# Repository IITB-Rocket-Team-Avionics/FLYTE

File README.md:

# FLYTE
Flight Computer for the IIT Bombay Rocket Team

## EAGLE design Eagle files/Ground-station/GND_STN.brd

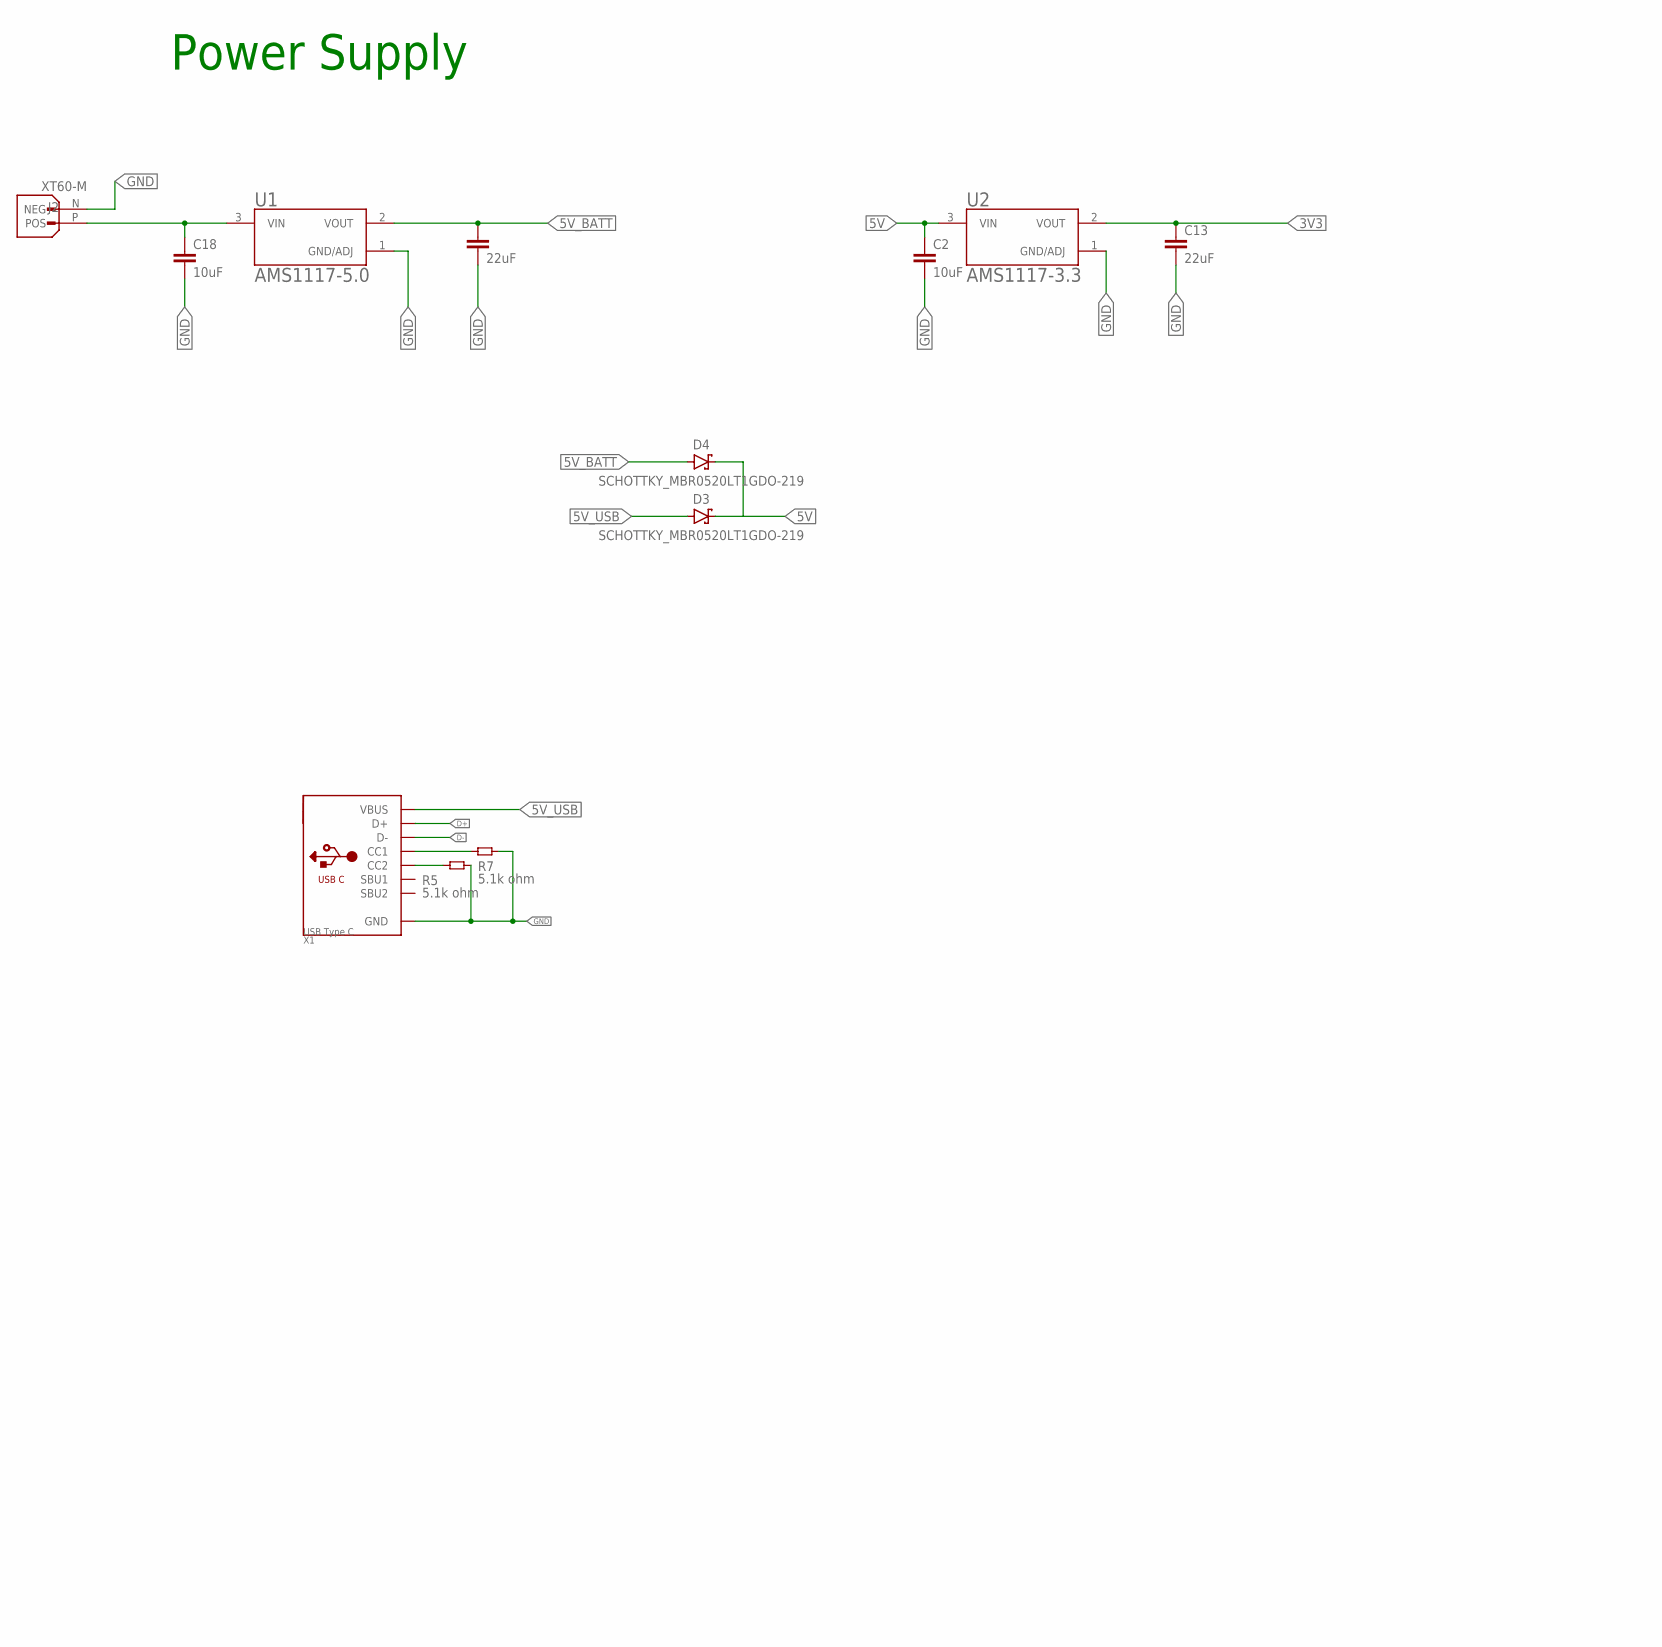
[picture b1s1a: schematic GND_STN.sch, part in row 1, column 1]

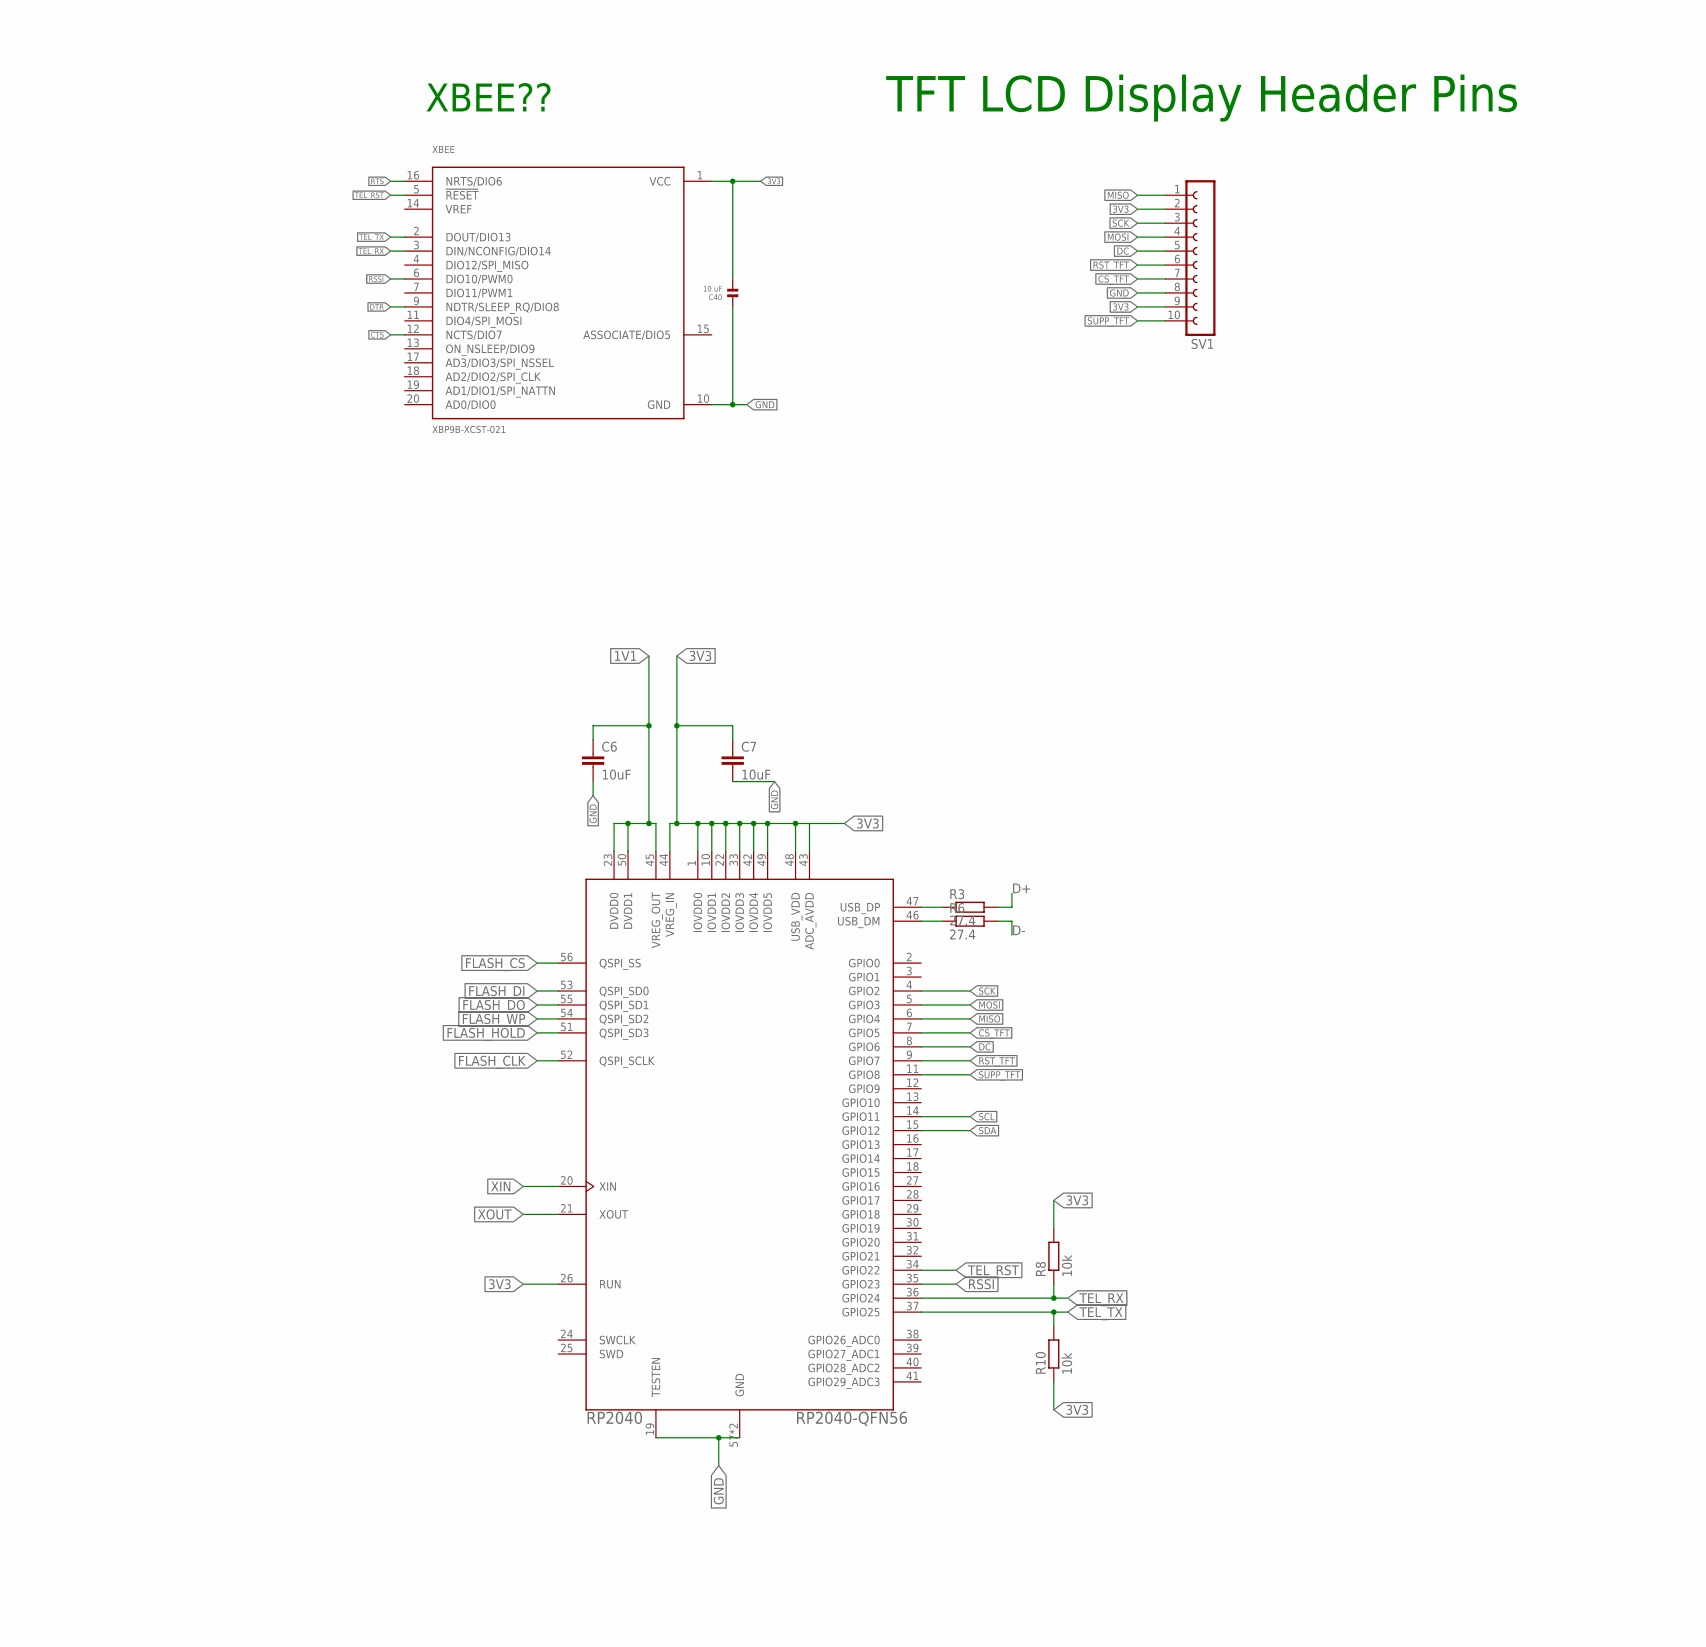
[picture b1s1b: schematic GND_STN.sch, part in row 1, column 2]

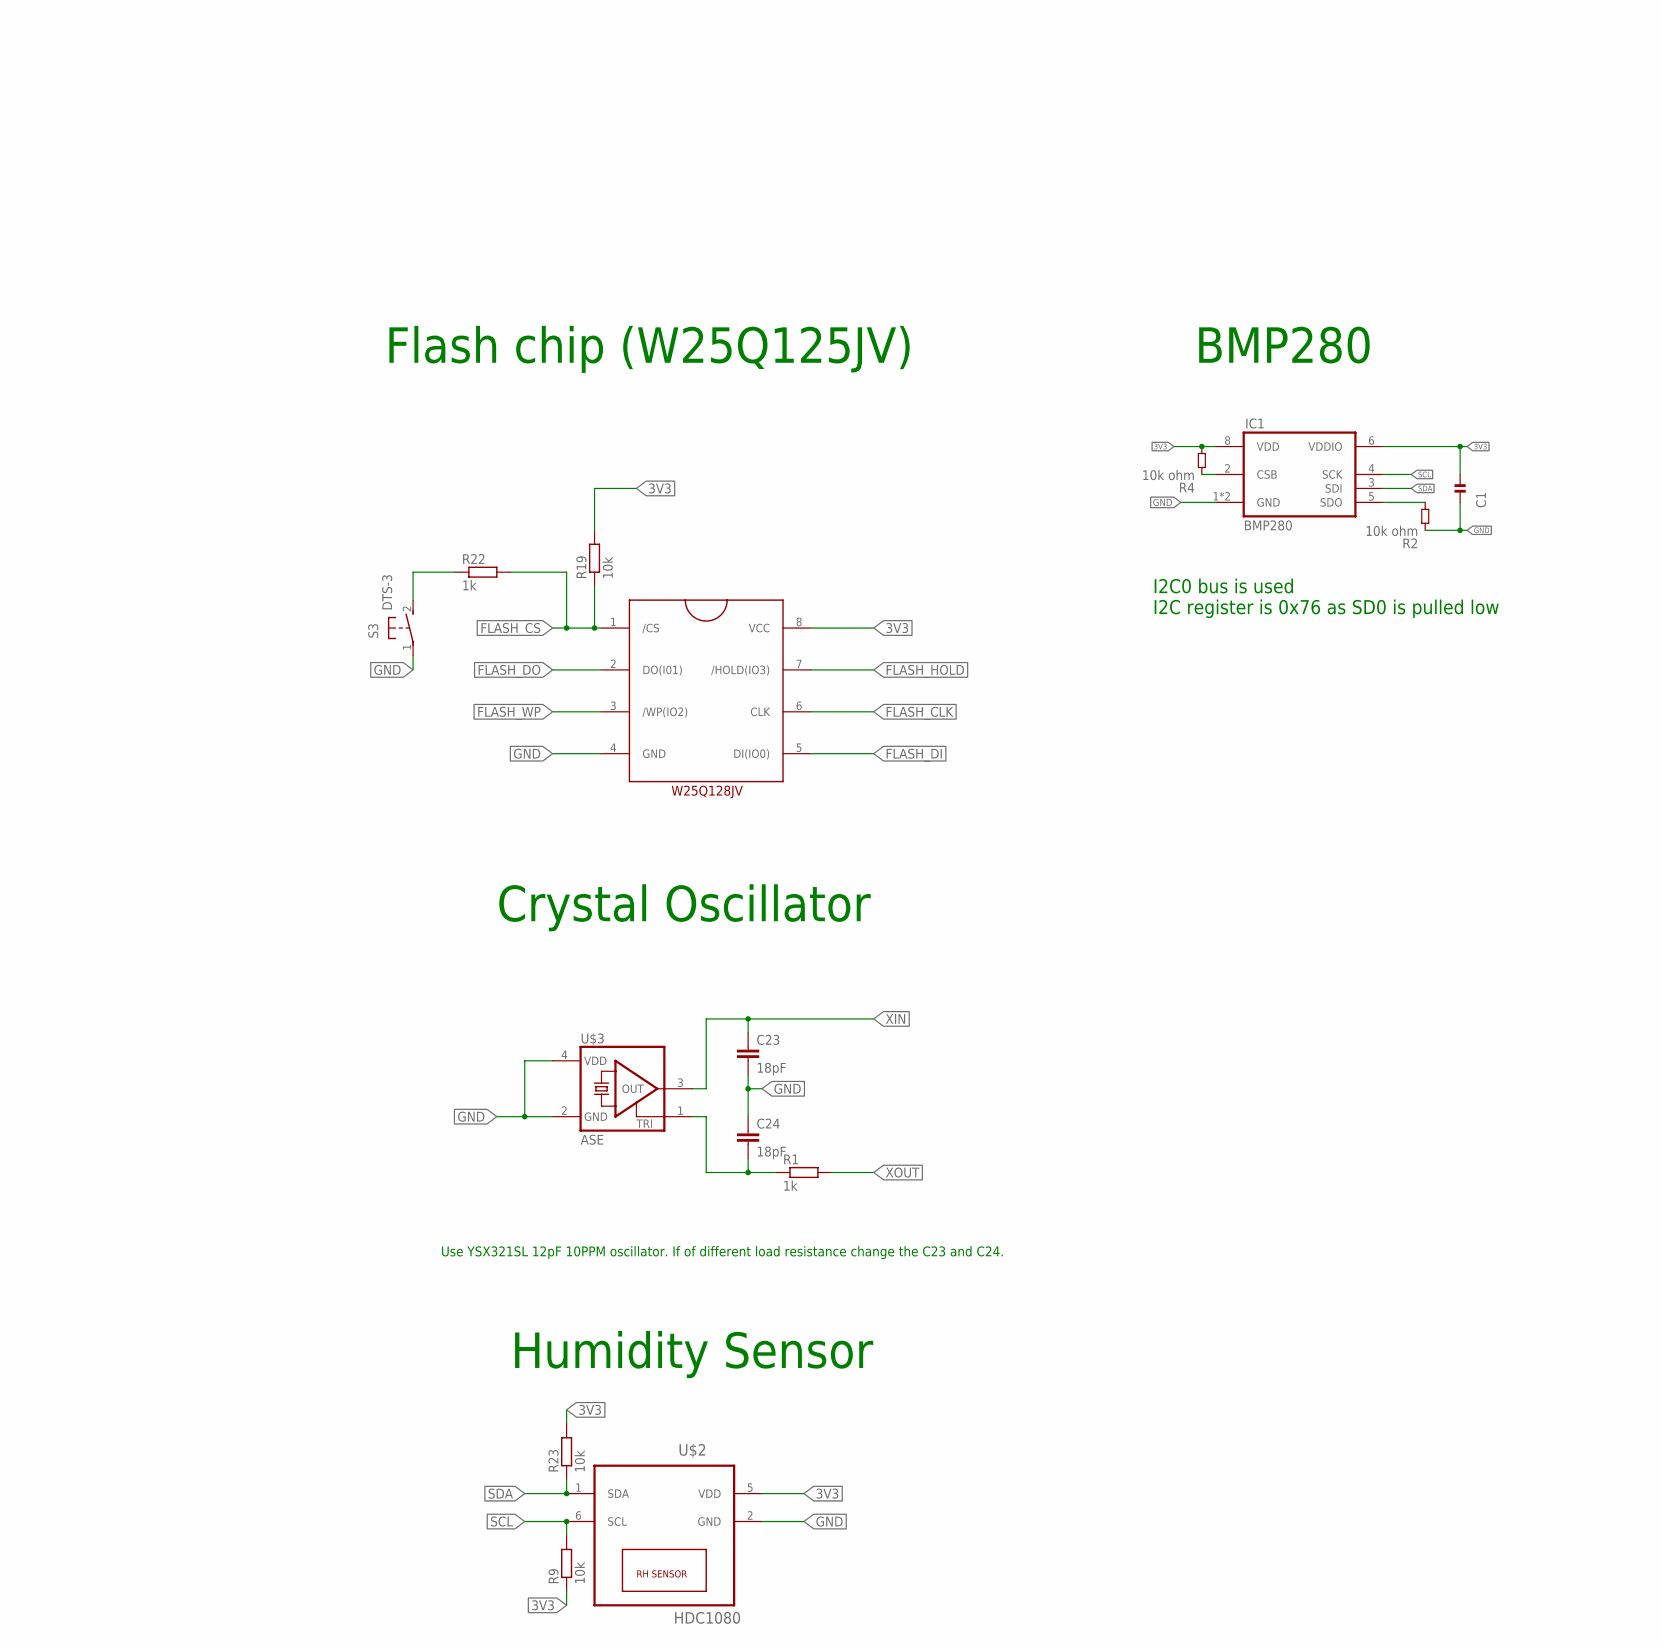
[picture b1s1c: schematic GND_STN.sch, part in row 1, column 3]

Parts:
C1, C40: 10 uF; 0603
C2, C6, C7, C18: 10uF; C0603
C3, C13: 22uF; C0603
C23, C24: 18pF; C0805
D3, D4: SCHOTTKY_MBR0520LT1GDO-219; SODFL3718X115
IC1: BMP280
J2: XT60-M; AMASS_XT60-M
R1: 1k; R0805
R2, R4: 10k ohm; 0603
R3, R6: 27.4; R0603
R5, R7: 5.1k ohm; 0603
R8, R9, R10, R19, R23: 10k; R0603
R22: 1k; R0603
RP2040: RP2040-QFN56; RP2040-QFN-56
S3: DTS-3
SV1: FE10-1; FE10
U1: AMS1117-5.0; SOT229P700X180-4N
U2: AMS1117-3.3; SOT229P700X180-4N
U4: SOIC127P790X216-8NW25Q128JVJSQ; SOIC127P790X216-8N
U$2: HDC1080; TI-S-PWSON-N6
U$3: ASE
X1: USB Type C; USB_C_CUSB31-CFM2AX-01-X
XBEE: XBP9B-XCST-021; DIP2200W51P200L3294H279Q20P

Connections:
1V1: C6.1, RP2040.23 (DVDD0), RP2040.45 (VREG_OUT), RP2040.50 (DVDD1)
3V3: C1.2, C7.1, C13.1, C40.2, IC1.6 (VDDIO), IC1.8 (VDD), R4.2, R8.2, R9.1, R10.1, R19.2, R23.2, RP2040.1 (IOVDD0), RP2040.10 (IOVDD1), RP2040.22 (IOVDD2), RP2040.26 (RUN), RP2040.33 (IOVDD3), RP2040.42 (IOVDD4), RP2040.43 (ADC_AVDD), RP2040.44 (VREG_IN), RP2040.48 (USB_VDD), RP2040.49 (IOVDD5), SV1.2, SV1.9, U2.2 (VOUT), U4.8 (VCC), U$2.5 (VDD), XBEE.1 (VCC)
5V: C2.1, D3.1 (C), D4.1 (C), U2.3 (VIN)
5V_BATT: C3.1, D4.2 (A), U1.2 (VOUT)
5V_USB: D3.2 (A), X1.A4B9 (VBUS), X1.B4A9 (VBUS)
CC3: R5.1, X1.B5 (CC2)
CC4: R7.1, X1.A5 (CC1)
CSB: IC1.2 (CSB), R4.1
CS_TFT: RP2040.7 (GPIO5), SV1.7
CTS: XBEE.12 (NCTS/DIO7)
D+: R3.2, X1.A6 (D+), X1.B6 (D+)
D-: R6.2, X1.A7 (D-), X1.B7 (D-)
DC: RP2040.8 (GPIO6), SV1.5
DTR: XBEE.9 (NDTR/SLEEP_RQ/DIO8)
FLASH_CLK: RP2040.52 (QSPI_SCLK), U4.6 (CLK)
FLASH_CS: R19.1, R22.2, RP2040.56 (QSPI_SS), U4.1 (/CS)
FLASH_DI: RP2040.53 (QSPI_SD0), U4.5 (DI(IO0))
FLASH_DO: RP2040.55 (QSPI_SD1), U4.2 (DO(I01))
FLASH_HOLD: RP2040.51 (QSPI_SD3), U4.7 (/HOLD(IO3))
FLASH_WP: RP2040.54 (QSPI_SD2), U4.3 (/WP(IO2))
GND: C1.1, C2.2, C3.2, C6.2, C7.2, C13.2, C18.2, C23.2, C24.1, C40.1, IC1.1 (GND), IC1.7 (GND), J2.N (NEG), R2.1, R5.2, R7.2, RP2040.19 (TESTEN), RP2040.57 (GND), RP2040.62 (GND), S3.1, SV1.8, U1.1 (GND/ADJ), U2.1 (GND/ADJ), U4.4 (GND), U$2.2 (GND), U$3.2 (GND), U$3.4 (VDD), X1.A1B12 (GND), X1.B1A12 (GND), XBEE.10 (GND)
MISO: RP2040.6 (GPIO4), SV1.1
MOSI: RP2040.5 (GPIO3), SV1.4
unnamed: R22.1, S3.2
unnamed: R3.1, RP2040.47 (USB_DP)
unnamed: R6.1, RP2040.46 (USB_DM)
unnamed: C24.2, R1.1, U$3.1 (TRI)
unnamed: C18.1, J2.P (POS), U1.3 (VIN)
RSSI: RP2040.35 (GPIO23), XBEE.6 (DIO10/PWM0)
RST_TFT: RP2040.9 (GPIO7), SV1.6
RTS: XBEE.16 (NRTS/DIO6)
SCK: RP2040.4 (GPIO2), SV1.3
SCL: IC1.4 (SCK), R9.2, RP2040.14 (GPIO11), U$2.6 (SCL)
SDA: IC1.3 (SDI), R23.1, RP2040.15 (GPIO12), U$2.1 (SDA)
SDO1: IC1.5 (SDO), R2.2
SUPP_TFT: RP2040.11 (GPIO8), SV1.10
TEL_RST: RP2040.34 (GPIO22), XBEE.5 (!RESET)
TEL_RX: R8.1, RP2040.36 (GPIO24), XBEE.3 (DIN/NCONFIG/DIO14)
TEL_TX: R10.2, RP2040.37 (GPIO25), XBEE.2 (DOUT/DIO13)
XIN: C23.1, RP2040.20 (XIN), U$3.3 (OUT)
XOUT: R1.2, RP2040.21 (XOUT)

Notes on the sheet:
Flash chip (W25Q125JV)
Power Supply
Crystal Oscillator
Use YSX321SL 12pF 10PPM oscillator. If of different load resistance change the C23 and C24.
I2C0 bus is used I2C register is 0x76 as SD0 is pulled low
BMP280
Humidity Sensor
TFT LCD Display Header Pins
XBEE??

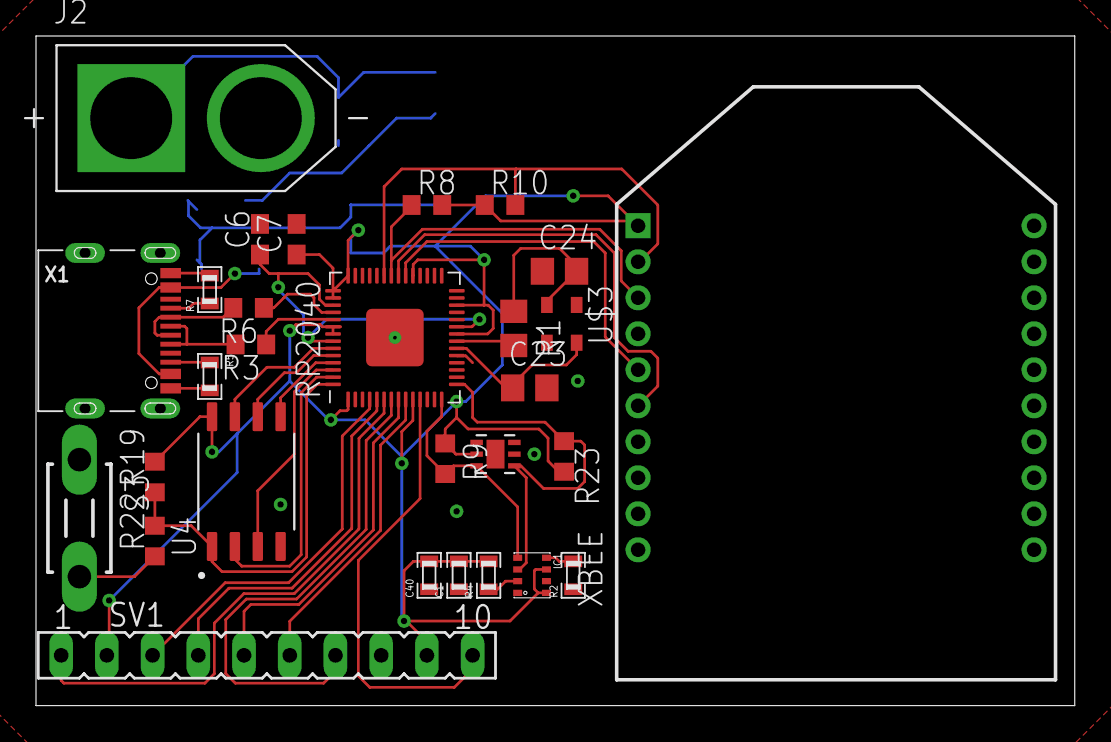
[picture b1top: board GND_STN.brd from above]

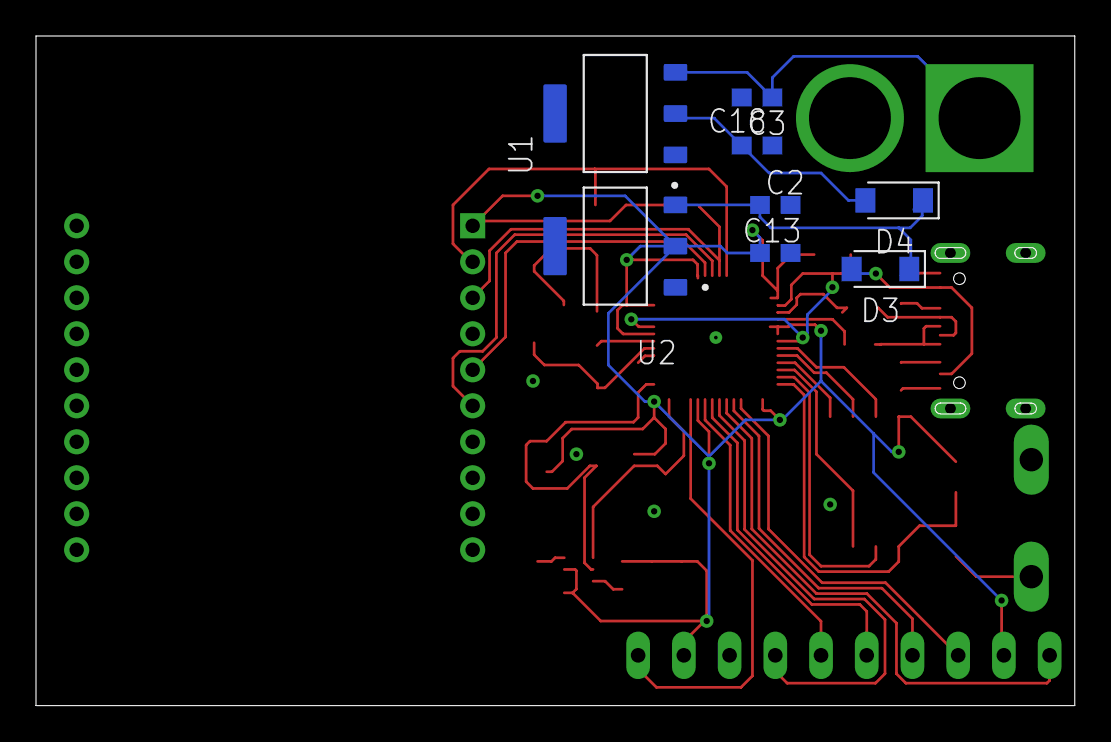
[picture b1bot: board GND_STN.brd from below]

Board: 2 copper layers, 57.7 x 37.2 mm, 37 parts (8 on the bottom side), 38 nets.

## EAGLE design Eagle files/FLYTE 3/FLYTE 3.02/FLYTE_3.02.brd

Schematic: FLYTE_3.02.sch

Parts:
AC1: KX134-1211; KX1341211
BOOT: DTSM-3
BUZZER: BUZZER; CUI_CMT-8530S-SMT
C1, C4, C5, C7, C8, C9, C10, C11, C12, C13, C14, C15, C16, C17, C19, C20, C21, C25, C26, C30, C31, C32, C34, C40, C42, C52, C62, C63: 10 uF; 0603
C2, C3: 18 pF; 0603
C6: 100 pF; 0603
C18, C27: 10\ uF; 0603
C22, C101: 100 nF; 0603
C23, C24: 27 pF; 0603
C28: 470 pF; 0603
C33, C35, C37: 120 pF; 0603
D2, D9, D10, D13: RSX501LAM20TR; SODFL4725X105N
D3, D4, D5, D6, D7, D11, D12: LED.0603; 0603.LED
FIN_1, FIN_2, FIN_3, FIN_4: 03-JST-B3B-XH-A; B3B-XH
FLASH: W25Q128JVSIQ; SOIC127P790X216-8N
GNSS: TESEO-LIV3F; SON110P970X1010X230-18N
IC1: BMP280
IC2: MPXV5100DP
IC9: MCP73844-840I_MS; SOP65P490X110-8N
J1, J3: JST-XH-2B; B2B-XH-A
J2: CON-SMA-EDGE-S; RFSOLUTIONS_CON-SMA-EDGE-S
J7: XT60-M; AMASS_XT60-M
L1: RF-INDUCTOR.0603; 0603
L2: ASPI-0630LR-220M-T15; IND_ASPI-0630LR-220M-T15
L3: 22 uH; 0603
LED: LED.0603; 0603.LED
MOTOR: 03-JST-B3B-XH-A; B3B-XH
Q1, Q3, Q4: SI7625DN-T1-GE3; SIS862DNT1GE3
Q2, Q5: MOSFET-PWIDE; SOT23-WIDE
R0, R9, R10, R11, R13, R14, R15, R17, R21, R23, R26, R30, R33, R36, R38, R46, R47, R53, R54, R55, R56, R57, R60, R61, R62, R66, R67, R68, R69, R70, R71, R72, R73, R74, R75, R76, R77, R78, R79, R80, R81, R82, R86, R87, R88, R89, R90, R91, R92, R93, R94, R95, R100, R101, R113, R114: 10k ohm; 0603
R1, R5: 1k ohm; 0603
R2, R8, R19, R29, R34, R44, R58: 100 ohm; 0603
R3, R4: 27.4 ohm; 0603
R6, R7: 5.1k ohm; 0603
R12, R22, R28, R32: 45k ohm; 0603
R16: 145k ohm; 0603
R24, R25, R27, R31, R35, R63: 0.13 ohm; 0603
R37: 30k ohm; 0603
R39, R40, R42, R43, R115, R116, R117: 0 ohm; 0603
R41: 0 ohm; 0805
R45: 190k ohm; 0603
R59: 315 ohm; 0603
R65: 100k ohm; 0603
RP2040: RP2040-QFN56; RP2040-QFN-56
SAW: SAW_FILTER; FIL_AFS14A04-1575.42-T3
U1: BNO055; LGA28R50P4X10_380X520X100
U2, U3, U5, U7, U10: CJ3400; SOT91P240X120-3N
U4: LM1117-3.3; SOT230
U6, U9, U15, U16: ADS1115IDGSR; SOP50P490X110-10N
U8, U11, U13, U14, U17: MIC29302WU-TRTO-263-5_MCH-L; TO-263-5_MCH-L
U12: CP2102; QFN50P500X500X100-29N
U19, U22: MT3608; SOT95P280X145-6N
U20: AP2210K-3.3TRG1; SOT-23-5_RAW
U$3: SN74LVC1G04DBVR; SOT23-5
X1: 22-23-2121
X6: USB Type C; USB_C_CUSB31-CFM2AX-01-X
XBEE: XBP9B-XCST-021; DIP2200W51P200L3294H279Q20P
XTAL: ASE
Y1: FC-135_32.7680KA-A0; XTAL_FC-135_32.7680KA-A0

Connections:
1V1: C8.2, RP2040.23 (DVDD0), RP2040.45 (VREG_OUT), RP2040.50 (DVDD1)
3V3: C4.2, C40.2, R39.2, R40.1, R93.2, R94.2, U4.2 (VOUT), U4.4 (VOUT_2), XBEE.1 (VCC)
3V3_OP: AC1.1 (SDO/ADDR), AC1.3 (IO_VDD), AC1.7 (VDD), AC1.10 (NCS), C10.2, C20.2, C21.1, C30.2, C32.2, FLASH.8 (VCC), GNSS.6 (VBATT), GNSS.7 (VCC_IO), GNSS.8 (VCC), IC1.6 (VDDIO), IC1.8 (VDD), R0.2, R10.2, R14.1, R39.1, R73.2, R80.2, R81.2, R82.2, R101.2, RP2040.1 (IOVDD0), RP2040.10 (IOVDD1), RP2040.22 (IOVDD2), RP2040.26 (RUN), RP2040.33 (IOVDD3), RP2040.42 (IOVDD4), RP2040.43 (ADC_AVDD), RP2040.44 (VREG_IN), RP2040.48 (USB_VDD), RP2040.49 (IOVDD5), U1.3 (VDD), U1.4 (NBOOT_LOAD_PIN), U1.28 (VDDIO), U15.7 (AIN3)
3V3_SET: C62.1, R40.2, R100.1, U12.6 (VDD)
5V: C5.2, C17.1, C26.1, IC2.2 (VS), L1.1, MOTOR.P$2, U6.8 (VDD), U9.1 (ADDR), U9.8 (VDD), U15.8 (VDD), U16.8 (VDD), U20.5 (VOUT)
BC: Q2.1 (G), R70.2, U$3.2 (A), X1.11
BUZZER: R72.2, RP2040.2 (GPIO0), U10.1 (G)
CAM: D12.P$1 (1), RP2040.4 (GPIO2), U8.1 (EN)
CC1: R7.1, X6.A5 (CC1)
CC2: R6.1, X6.B5 (CC2)
CSB: IC1.2 (CSB), R10.1
CTRL: D6.P$1 (1), RP2040.5 (GPIO3), U11.1 (EN), U13.1 (EN), U14.1 (EN), U17.1 (EN)
CTS: R115.1, XBEE.12 (NCTS/DIO7)
D1: C11.2, FIN_1.P$2, R25.2, R55.1
D2: C9.2, FIN_2.P$2, R27.2, R68.1
D3: C14.2, FIN_3.P$2, R31.2, R77.1
D4: C16.2, FIN_4.P$2, R35.2, R89.1
D+: R3.2, R41.1, X6.A6 (D+), X6.B6 (D+)
D+1: R41.2, U12.4 (D+)
D-: R4.2, U12.5 (D-), X6.A7 (D-), X6.B7 (D-)
DROGUE: R15.2, RP2040.29 (GPIO18), U5.1 (G)
DTR: R117.1, XBEE.9 (NDTR/SLEEP_RQ/DIO8)
FIN_1: FIN_1.P$1, RP2040.9 (GPIO7)
FIN_2: FIN_2.P$1, RP2040.8 (GPIO6)
FIN_3: FIN_3.P$1, RP2040.7 (GPIO5)
FIN_4: FIN_4.P$1, RP2040.6 (GPIO4)
GND: AC1.4 (TRIG), AC1.8 (GND_1), AC1.9 (GND_2), BOOT.1, C1.1, C2.1, C3.1, C4.1, C5.1, C6.1, C7.1, C8.1, C9.1, C10.1, C11.1, C12.2, C13.2, C14.1, C15.2, C16.1, C17.2, C18.1, C19.2, C20.1, C21.2, C22.1, C23.2, C24.2, C25.1, C26.2, C27.1, C28.1, C30.1, C31.1, C32.1, C34.2, C35.2, C40.1, C42.1, C52.1, C62.2, C63.2, C101.1, FIN_1.P$3, FIN_2.P$3, FIN_3.P$3, FIN_4.P$3, FLASH.4 (GND), GNSS.1 (GND), GNSS.10 (GND_RF_1), GNSS.12 (GND_RF_2), IC1.1 (GND), IC1.7 (GND), IC2.3 (GND), IC9.6 (VSS), J1.2, J2.G1 (2), J2.G2 (2), J2.G3 (2), J2.G4 (2), J3.2, J7.N (NEG), MOTOR.P$3, R2.2, R6.2, R7.2, R8.2, R9.1, R11.1, R13.1, R15.1, R17.2, R19.2, R21.1, R23.1, R26.1, R29.1, R30.1, R33.1, R34.1, R36.1, R38.1, R44.1, R46.2, R47.1, R54.2, R56.2, R58.2, R59.2, R60.2, R62.2, R67.2, R69.2, R72.1, R74.2, R76.2, R78.2, R86.2, R88.2, R90.2, R92.2, R95.1, R100.2, R101.1, R114.2, RP2040.19 (TESTEN), RP2040.57 (GND), RP2040.62 (GND), SAW.B (GND), SAW.D (GND), SAW.E (GND), U1.2 (GND), U1.5 (PS1), U1.6 (PS0), U1.10 (PIN10), U1.15 (PIN15), U1.16 (PIN16), U1.18 (COM2), U1.25 (GNDIO), U2.2 (S), U3.2 (S), U4.1 (ADJ/GND), U5.2 (S), U6.1 (ADDR), U6.3 (GND), U7.2 (S), U8.3 (GND), U8.6, U9.3 (GND), U11.3 (GND), U11.6, U12.3 (GND), U12.29 (GND), U13.3 (GND), U13.6, U14.3 (GND), U14.6, U15.3 (GND), U16.3 (GND), U17.3 (GND), U17.6, U19.2 (GND), U20.2 (GND), U22.2 (GND), U$3.3 (GND), X1.12, X6.A1B12 (GND), X6.B1A12 (GND), XBEE.10 (GND), XTAL.2 (GND), XTAL.4 (VDD)
GPS_RX: GNSS.3 (RX), R81.1, RP2040.27 (GPIO16)
GPS_TX: GNSS.2 (TX), R82.1, RP2040.28 (GPIO17)
IGN1: R36.2, RP2040.31 (GPIO20), U3.1 (G)
IGN2: R26.2, RP2040.32 (GPIO21), U2.1 (G)
LED: LED.P$1 (1), RP2040.3 (GPIO1)
MAIN: R21.2, RP2040.30 (GPIO19), U7.1 (G)
MOS: D4.P$1 (1), D13.2 (A), Q1.5 (D_1), Q1.6 (D_2), Q1.7 (D_3), Q1.8 (D_4), Q1.9 (D_5), Q1.10 (D_6), Q1.11 (D_7), X1.10
unnamed: LED.P$2 (2), R2.1
unnamed: C3.2, R5.1, XTAL.1 (TRI)
unnamed: C33.1, GNSS.11 (RF_IN)
unnamed: R12.2, R13.2, U11.5 (ADJ)
unnamed: BUZZER.N, R8.1
unnamed: D12.P$2 (2), R19.1
unnamed: IC9.1 (SENSE), Q3.1 (S_1), Q3.2 (S_2), Q3.3 (S_3), Q4.1 (S_1), Q4.2 (S_2), Q4.3 (S_3), R24.1, R63.1
unnamed: BUZZER.P, U10.2 (S)
unnamed: C22.2, U1.9 (CAP)
unnamed: R11.2, U1.17 (COM3)
unnamed: R22.2, R23.2, U13.5 (ADJ)
unnamed: R28.2, R30.2, U14.5 (ADJ)
unnamed: R32.2, R33.2, U17.5 (ADJ)
unnamed: R14.2, U1.11 (NRESET)
unnamed: D11.P$2 (2), IC9.3 (STAT1)
unnamed: C35.1, C37.2, J2.1, L1.2
unnamed: D10.2 (A), L2.2, U19.1 (SW)
unnamed: R16.2, R17.1, U19.3 (FB)
unnamed: R55.2, R56.1, U6.5 (AIN1)
unnamed: R53.2, R54.1, U6.4 (AIN0)
unnamed: C37.1, SAW.C (IN)
unnamed: D3.P$2 (2), R44.2
unnamed: C33.2, SAW.A (OUT)
unnamed: R113.2, U12.9 (!RST)
unnamed: R37.2, R38.2, U8.5 (ADJ)
unnamed: R57.2, R60.1, U6.6 (AIN2)
unnamed: R61.2, R62.1, U6.7 (AIN3)
unnamed: R66.2, R67.1, U9.4 (AIN0)
unnamed: R68.2, R69.1, U9.5 (AIN1)
unnamed: R71.2, R74.1, U9.6 (AIN2)
unnamed: R75.2, R76.1, U15.4 (AIN0)
unnamed: R77.2, R78.1, U15.5 (AIN1)
unnamed: R79.2, R86.1, U15.6 (AIN2)
unnamed: R87.2, R88.1, U16.4 (AIN0)
unnamed: R89.2, R90.1, U16.5 (AIN1)
unnamed: R91.2, R92.1, U16.6 (AIN2)
unnamed: R114.1, U12.11 (!SUSPEND)
unnamed: R115.2, U12.23 (CTS)
unnamed: R116.2, U12.24 (RTS)
unnamed: R117.2, U12.28 (DTR)
unnamed: C6.2, U20.4 (BYP)
unnamed: D9.2 (A), L3.2, U22.1 (SW)
unnamed: R45.2, R46.1, U22.3 (FB)
unnamed: C27.2, D9.1 (K), Q1.4 (G), R45.1
unnamed: D4.P$2 (2), R29.2
unnamed: D5.P$2 (2), R34.2
unnamed: D6.P$2 (2), R58.1
unnamed: D7.P$2 (2), R59.1
unnamed: IC9.4 (EN), R65.1
unnamed: IC9.8 (DRV), Q3.4 (G), Q4.4 (G)
unnamed: C101.2, IC9.5 (TIMER)
unnamed: Q5.1 (G), U$3.4 (Y)
PYRO_DROGUE: R57.1, U5.3 (D), X1.2
PYRO_IGN1: R79.1, U3.3 (D), X1.6
PYRO_IGN2: R91.1, U2.3 (D), X1.8
PYRO_MAIN: R71.1, U7.3 (D), X1.4
QSPI_SCLK: FLASH.6 (CLK), RP2040.52 (QSPI_SCLK)
QSPI_SD0: FLASH.5 (DI(IO0)), RP2040.53 (QSPI_SD0)
QSPI_SD1: FLASH.2 (DO(IO1)), RP2040.55 (QSPI_SD1)
QSPI_SD2: FLASH.3 (/WP(IO2)), RP2040.54 (QSPI_SD2)
QSPI_SD3: FLASH.7 (/HOLD/RESET(IO3)), RP2040.51 (QSPI_SD3)
QSPI_SS: FLASH.1 (/CS), R0.1, R1.2, RP2040.56 (QSPI_SS)
RSSI: RP2040.35 (GPIO23), XBEE.6 (DIO10/PWM0)
RTS: R116.1, XBEE.16 (NRTS/DIO6)
SCL: AC1.12 (SCLK/SCL), IC1.4 (SCK), R73.1, RP2040.16 (GPIO13), U1.19 (COM1), U6.10 (SCL), U9.10 (SCL), U15.1 (ADDR), U15.10 (SCL), U16.10 (SCL)
SDA: AC1.2 (SDI/SDA), IC1.3 (SDI), R80.1, RP2040.15 (GPIO12), U1.20 (COM0), U6.9 (SDA), U9.9 (SDA), U15.9 (SDA), U16.1 (ADDR), U16.9 (SDA)
SDO: IC1.5 (SDO), R9.2
TEL_RST: RP2040.34 (GPIO22), XBEE.5 (!RESET)
TEL_RX: R93.1, RP2040.36 (GPIO24), U12.26 (TXD), XBEE.3 (DIN/NCONFIG/DIO14)
TEL_TX: R94.1, RP2040.37 (GPIO25), U12.25 (RXD), XBEE.2 (DOUT/DIO13)
USB+: C25.2, L3.1, Q2.2 (S), Q5.2 (S), R47.2, R70.1, U22.4 (EN), U22.5 (IN), U$3.1 (NC), U$3.5 (VCC), X6.A4B9 (VBUS), X6.B4A9 (VBUS)
USB_BOOT: BOOT.2, R1.1
USB_BST: C18.2, D10.1 (K), D11.P$1 (1), IC9.2 (VDD), R16.1, R24.2, R63.2, R65.2
USB_CHG: C52.2, L2.1, Q2.3 (D), R95.2, U19.4 (EN), U19.5 (IN)
USB_DM: R4.1, RP2040.46 (USB_DM)
USB_DP: R3.1, RP2040.47 (USB_DP)
VBUS: Q5.3 (D), R42.1, R43.2
VBUS_OP: D2.2 (A), D5.P$1 (1), R42.2
VBUS_SET: C63.1, D3.P$1 (1), R43.1, R113.1, U12.7 (REGIN), U12.8 (VBUS)
VCC: C1.2, C7.2, C34.1, D2.1 (K), D13.1 (K), U4.3 (VIN), U8.2 (IN), U10.3 (D), U20.1 (VIN), U20.3 (EN)
VCC_PYRO: D7.P$1 (1), X1.1, X1.3, X1.5, X1.7, X1.9
VOLT_DP: C28.2, IC2.4 (VOUT), U16.7 (AIN3)
VOLT_MOTOR: MOTOR.P$1, U9.7 (AIN3)
V_CAM: C31.2, J1.1, J3.1, R37.1, U8.4 (OUT)
V_FIN_1: R12.1, R25.1, R53.1, U11.4 (OUT)
V_FIN_2: R22.1, R27.1, R66.1, U13.4 (OUT)
V_FIN_3: R28.1, R31.1, R75.1, U14.4 (OUT)
V_FIN_4: R32.1, R35.1, R87.1, U17.4 (OUT)
XIN: C2.2, RP2040.20 (XIN), XTAL.3 (OUT)
XIN32: C23.1, U1.27 (XIN32), Y1.1
XOUT: R5.2, RP2040.21 (XOUT)
XOUT32: C24.1, U1.26 (XOUT32), Y1.2
XT60+: C12.1, C13.1, C15.1, C19.1, C42.2, IC9.7 (VBAT), J7.P (POS), Q1.1 (S_1), Q1.2 (S_2), Q1.3 (S_3), Q3.5 (D_1), Q3.6 (D_2), Q3.7 (D_3), Q3.8 (D_4), Q3.9 (D_5), Q3.10 (D_6), Q3.11 (D_7), Q4.5 (D_1), Q4.6 (D_2), Q4.7 (D_3), Q4.8 (D_4), Q4.9 (D_5), Q4.10 (D_6), Q4.11 (D_7), R61.1, U11.2 (IN), U13.2 (IN), U14.2 (IN), U17.2 (IN)

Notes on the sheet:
FLASH
USB
RP2040
CRYSTAL OSCILLATOR
VBUS : Power from USB D+ : Data line 1 D- : Data line 2 CC1 & CC2 : Not sure what they are for but both must be pulled to GND using 5.1k ohm resistors when using Type-C USB SHLD : Outer covering of female USB connector. Should be grounded GND : Ground Try to route D+ and D- so that the differential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
Power C9-C16 : Decoupling capacitors for RP2040. Must be placed close to the power pins. C8 must be close to Pin 45, C10 must be close to Pin 44, rest can be jumbled around as you may like. There is one decoupling capacitor less than number of power pins. Not sure why, that's just how it is in the 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
Power C5 - Decoupling capacitor for flash. Must pe placed close to the flash. Boot When CS is pulled LOW on startup by pressing the button, the flash boots up as a mass storage device (like an SD Card). This is similar to plugging in a USB cable into a Pico while holding the BOOTSEL button. As a pr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
Purchase Links LED : https://evelta.com/green-led-smd-0603-package/ Buzzer : https://www.sunrom.com/p/electromagnetic-passive-buzzer-3-5v-smd-pcb-mount-mlt-8530
Crystal oscillators need a load capacitance to osciallte at the right frequency. This particular chip needs 12 pF. So, 2 capacitors of 22 pF each are placed to give an equivalent load capacitance of 11 pF. 24 pF capacitors were not available, but these get the job done. 1k ohm resistor to ensure th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
TESEO-LIV3F : GNSS Chip TX & RX : For UART communication SCL & SDA : For I2C communication PPS : Time pulse from GNSS VCC_RF : Power output from chip to active antenna C20 & C22 : Blocks DC voltage C18 & C21 : Decoupling capacitors GNSS_SWITCH : Used to switch between 3 antennae V1 : 0, V2 : 0 - RF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
GNSS
Telemetry communicates with pico on SPI0 bus

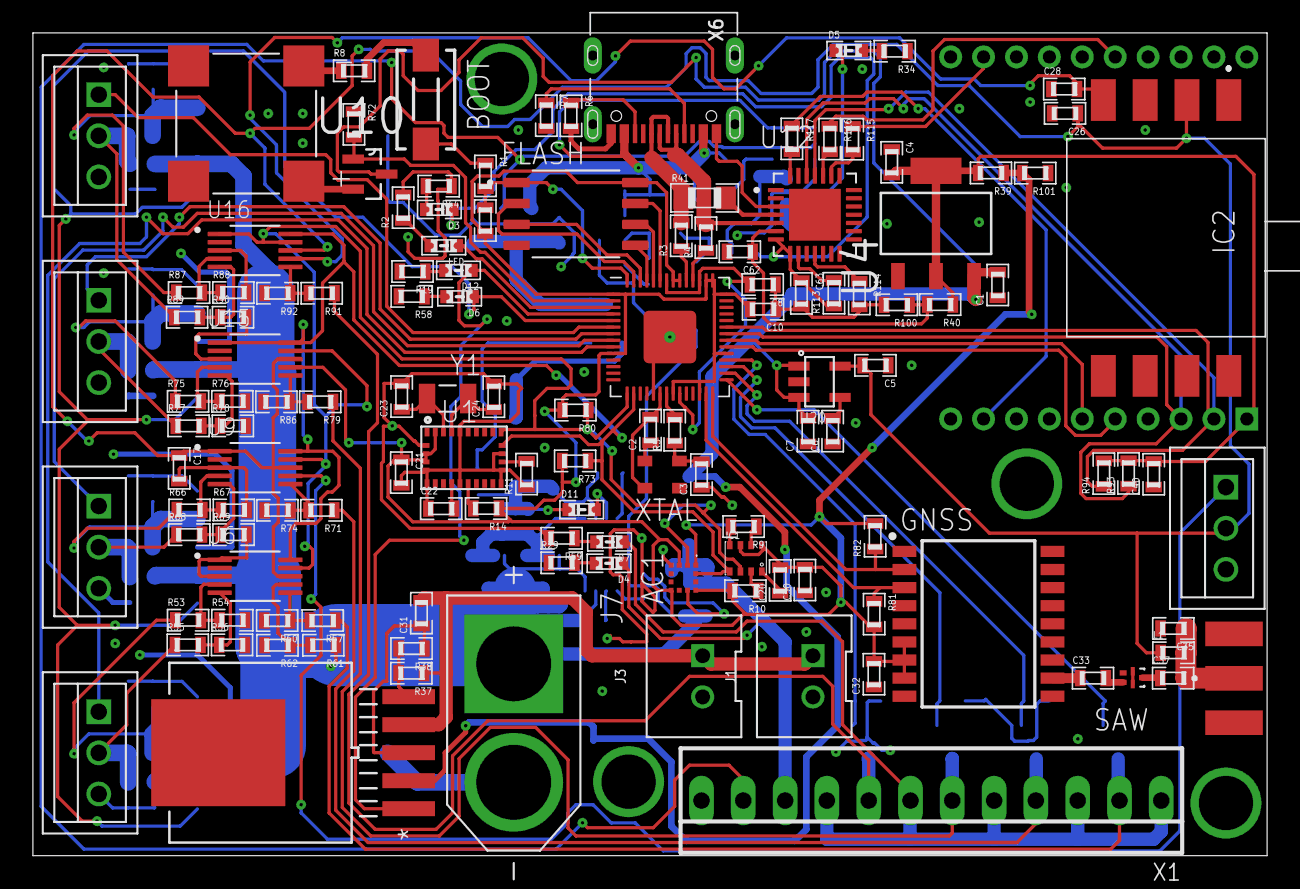
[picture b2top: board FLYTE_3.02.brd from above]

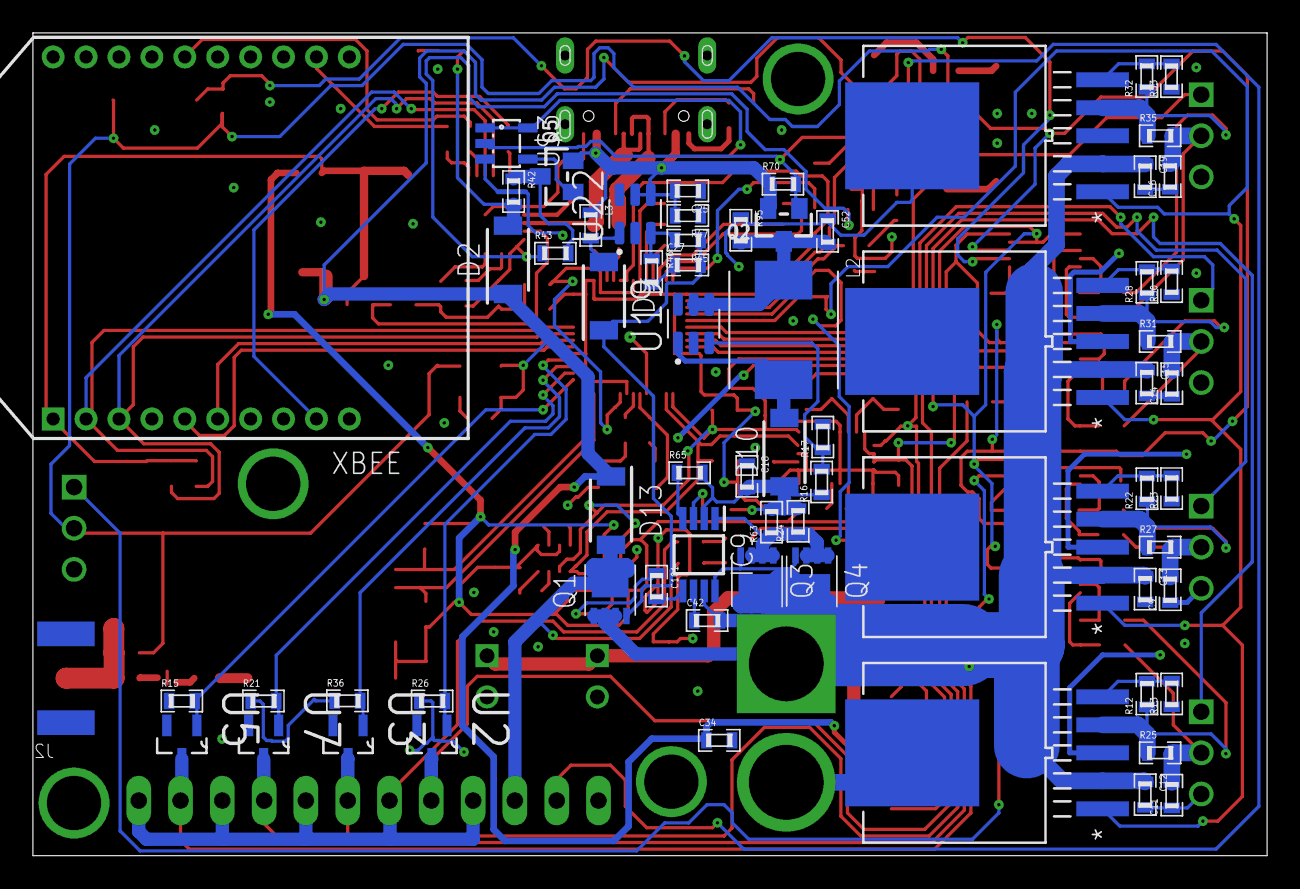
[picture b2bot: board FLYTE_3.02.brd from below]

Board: 2 copper layers, 75.0 x 50.0 mm, 198 parts (67 on the bottom side), 127 nets.

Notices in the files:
parts and their libraries:
SparkFun-Capacitors: Licensing: Creative Commons ShareAlike 4.0 International - https://creativecommons.org/licenses/by-sa/4.0
microbuilder: This work is placed in the public domain, and may be freely used for commercial and non-commercial work with the following conditions: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
